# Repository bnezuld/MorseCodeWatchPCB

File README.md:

# MorseCodeWatchPCB

KiCad PCB built for my [Morse Code Smart Watch project](https://github.com/bnezuld/ble_app_morsecode_watch)

with a [Bill of Material](https://github.com/bnezuld/MorseCodeWatchPCB/blob/master/MorseCodeWatch_bom.csv) of:
| Bill of material           |                         |                                                                                |               |
|--------------------------|----------------------------------|------------------------------------------------------------------------------|-----------------|
|PCB:                      |Morse Code Watch layout           |                                                                              |                 |
|Version:                  |1.1                               |                                                                              |                 |
|Designator                |Value                             |Description                                                                   |Footprint Doc    |
|C1, C2, C11, C12, C13, C14|12pF                              |Capacitor, NP0, ±2%                                                           |0402             |
|C3                        |0.8pF                             |Capacitor, NP0, ±5%                                                           |0402             |
|C4, C5, C8                |100nF                             |Capacitor, X7R, ±10%                                                          |0402             |
|C6                        |N.C.                              |Not mounted                                                                   |0402             |
|C7                        |100pF                             |Capacitor, NP0, ±5%                                                           |0402             |
|C9                        |4.7µF                             |Capacitor, X5R, ±10%                                                          |0603             |
|C10                       |1.0µF                             |Capacitor, X7R, ±10%                                                          |0603             |
|C15                       |22pF                              |                                                                              |0402             |
|C16,C17,C18               |10uF                              |                                                                              |0402             |
|C19                       |1.0µF                             |                                                                              |0402             |
|C20                       |2.2uF                             |                                                                              |0402             |
|L1                        |3.9nH                             |High frequency chip inductor ±5%                                              |0402             |
|U1                        |nRF52832-QFAA                     |Multi-protocol Bluetooth Low Energy, ANT and 2.4GHz proprietary system-on-chip|QFN-48           |
|X1                        |32MHz                             |XTAL SMD 2016, 32MHz, Cl=8pF, Total Tol: ±40ppm                               |XTAL_2016        |
|X2                        |32.768kHz                         |XTAL SMD 3215, 32.768kHz, Cl=9pF, Total Tol: ±50ppm                           |XTAL_3215        |
|R1                        |1K                                |                                                                              |0402             |
|R2,R3                     |10K                               |                                                                              |0402             |
|R4,R5                     |47ohm                             |                                                                              |0402             |
|R6                        |28K                               |                                                                              |0402             |
|U2                        |AT42QT1010                        |                                                                              |SOT-23-6         |
|U3                        |CAT24C256                         |                                                                              |Soic-8           |
|U4                        |MCP73831                          |                                                                              |SOT-23-5         |
|U5                        |DRV8836                           |                                                                              |WSON-12-1EP 3x2mm|
|U6                        |TPS78330                          |                                                                              |SOT-23-5         |
|D1                        |Red LED                           |                                                                              |0603             |
|D2                        |Green LED                         |                                                                              |0603             |
|SW1                       |DIP switch 5.08mm x 1.27mm        |                                                                              |                 |
|J1                        |2X5 1.27 mm pitch                 |                                                                              |                 |
|J2                        |USB B micro                       |                                                                              |                 |
|J3, J6                    |JST ACH 1x2                       |touchpad                                                                      |                 |
|J5                        |BatteryHolder Keystone 3034 1x20mm|battery                                                                       |                 |

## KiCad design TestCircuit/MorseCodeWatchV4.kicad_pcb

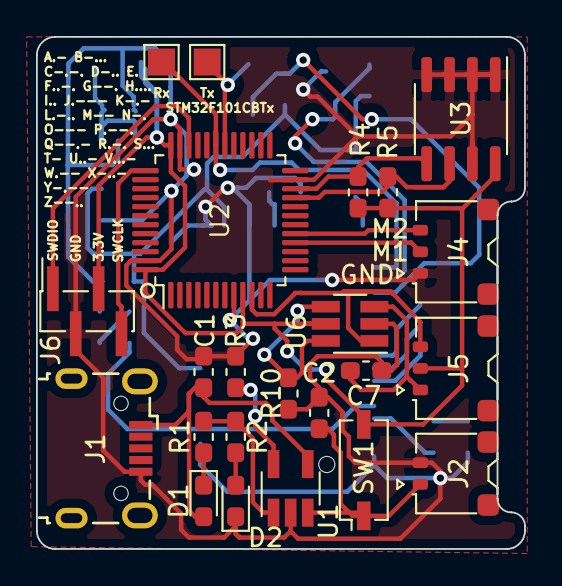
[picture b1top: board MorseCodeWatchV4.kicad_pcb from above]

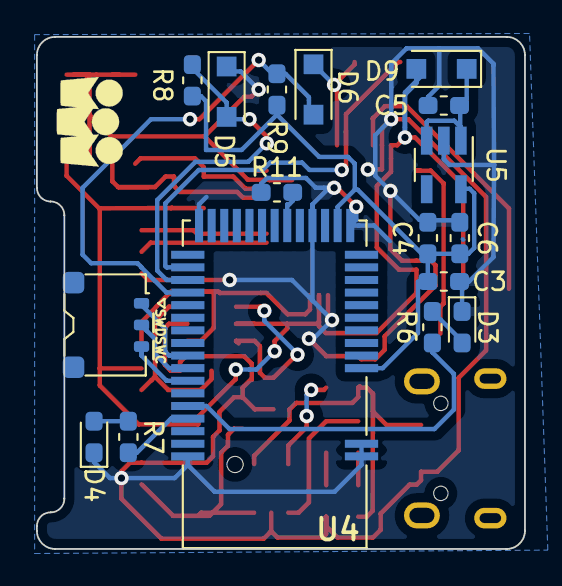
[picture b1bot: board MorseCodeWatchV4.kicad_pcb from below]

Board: 2 copper layers, 27.1 x 28.4 mm, 39 parts (16 on the bottom side), 28 nets.

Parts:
C1, C2: C 10uf; C_0603_1608Metric_Pad1.05x0.95mm_HandSolder
C3, C4: 1uF; C_0603_1608Metric_Pad1.05x0.95mm_HandSolder
C5, C6: 10uF; C_0603_1608Metric_Pad1.05x0.95mm_HandSolder
C7: 22pF; C_0603_1608Metric_Pad1.05x0.95mm_HandSolder
D1: LED RED; LED_0603_1608Metric_Pad1.05x0.95mm_HandSolder
D2: LED GREEN; LED_0603_1608Metric_Pad1.05x0.95mm_HandSolder
D3: LED RED; D_0603_1608Metric_Pad1.05x0.95mm_HandSolder
D4: LED BLUE; D_0603_1608Metric_Pad1.05x0.95mm_HandSolder
D5, D6: 1N4148; D_SOD-123F
D9: MBR120; D_SOD-123F
J1: USB_B_Micro; USB_Micro-B_Wuerth_629105150521
J2: Conn_01x02_Male LiPo Battery; JST_ACH_BM02B-ACHSS-GAN-ETF_1x02-1MP_P1.20mm_Vertical
J4, J5: Conn_01x03; JST_ACH_BM03B-ACHSS-GAN-ETF_1x03-1MP_P1.20mm_Vertical
J6: Conn_01x04_Female; PinHeader_1x04_P1.27mm_Vertical_SMD_Pin1Right
R1, R2, R4, R5: R; R_0603_1608Metric_Pad1.05x0.95mm_HandSolder
R3: R 10K; R_0603_1608Metric_Pad1.05x0.95mm_HandSolder
R6, R7, R10: 1K; R_0603_1608Metric_Pad1.05x0.95mm_HandSolder
R8, R9: 100K; R_0603_1608Metric_Pad1.05x0.95mm_HandSolder
R11: 2K; R_0603_1608Metric_Pad1.05x0.95mm_HandSolder
Rx: TestPoint_Pad_1.5x1.5mm
SW1: SW_DIP_x01; SW_DIP_SPSTx01_Slide_Copal_CHS-01A_W5.08mm_P1.27mm_JPin
Tx: TestPoint_Pad_1.5x1.5mm
U1: MCP73831-2-OT; SOT-23-5_HandSoldering
U2: STM32F101CBTx; LQFP-48_7x7mm_P0.5mm
U3: CAT24C256; SOIC-8_3.9x4.9mm_P1.27mm
U4: NRF51822_MODULE_MDBT40; BLE_MODULE_RAYTAC_MDBT40
U5: MIC5225-3.3; SOT-23-5_HandSoldering
U6: AT42QT1010-TSHR; SOT-23-6_Handsoldering

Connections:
3.3V: C3.1, C4.1, C6.1, R8.2, R9.2, U4.3, U4.14, U5.5
/CONNECTED_LED: R7.1, U4.39
/CTS_3V: D5.2, R8.1, U4.28
/MODE_3V: R11.1, U4.18
/MODE_LED: R6.1, U4.38
/MainSwitch: J5.3, U2.10, U6.1
/Motor1: J4.2, U2.16
/Motor2: J4.3, U2.17
/PROG: R3.1, U1.5
/Rx: Rx.1, U2.31, U4.27
/SCL: R4.2, U2.21, U3.6
/SDA: R5.2, U2.22, U3.5
/STAT: R1.2, R2.2, U1.1
/SWCLK: J6.4, U2.37
/SWDIO: J6.1, U2.34
/TOG-AHLB: R10.1, U6.4, U6.6
/TXD_3V: D6.2, R9.1, U4.29
/TouchPad: C7.1, J5.1, U6.3
/Tx: D6.1, Tx.1, U2.30
/VBAT: D9.2, J5.2, J6.3, R4.1, R5.1, SW1.2, U2.9, U2.24, U2.36, U2.48, U3.8, U6.5
/VBAT-IN: C2.1, J2.1, SW1.1, U1.3
/VCC: C1.1, D1.2, J1.1, U1.4
GND: C1.2, C2.2, C3.2, C4.2, C5.2, C6.2, C7.2, D2.1, D3.1, D4.1, D5.1, J1.5, J2.2, J4.1, J6.2, R3.2, R10.2, R11.2, U1.2, U2.8, U2.23, U2.35, U2.47, U3.1, U3.2, U3.3, U3.4, U3.7, U4.1, U4.2, U4.13, U4.16, U4.25, U4.42, U5.2, U6.2
unnamed: C5.1, D9.1, U5.1, U5.3
unnamed: D1.1, R1.1
unnamed: D2.2, R2.1
unnamed: D3.2, R6.2
unnamed: D4.2, R7.2

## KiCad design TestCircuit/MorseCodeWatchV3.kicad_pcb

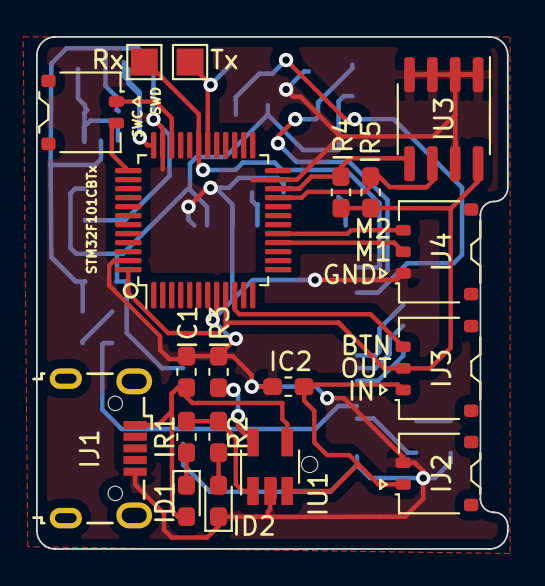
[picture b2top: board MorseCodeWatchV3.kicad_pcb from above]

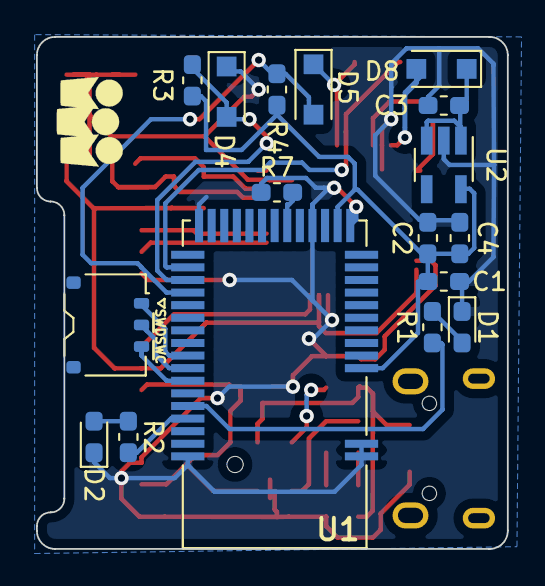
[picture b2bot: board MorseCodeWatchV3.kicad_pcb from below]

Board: 2 copper layers, 26.2 x 28.4 mm, 34 parts (16 on the bottom side), 24 nets.

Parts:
C1, C2: 1uF; C_0603_1608Metric_Pad1.05x0.95mm_HandSolder
C3, C4: 10uF; C_0603_1608Metric_Pad1.05x0.95mm_HandSolder
D1: RED; D_0603_1608Metric_Pad1.05x0.95mm_HandSolder
D2: GREEN; D_0603_1608Metric_Pad1.05x0.95mm_HandSolder
D4, D5, D8: MBR120; D_SOD-123F
IC1, IC2: C 10uf; C_0603_1608Metric_Pad1.05x0.95mm_HandSolder
ID1: LED RED; LED_0603_1608Metric_Pad1.05x0.95mm_HandSolder
ID2: LED GREEN; LED_0603_1608Metric_Pad1.05x0.95mm_HandSolder
IJ1: USB_B_Micro; USB_Micro-B_Wuerth_629105150521
IJ2: Conn_01x02_Male LiPo Battery; JST_ACH_BM02B-ACHSS-GAN-ETF_1x02-1MP_P1.20mm_Vertical
IJ3, IJ4: JST_ACH_BM03B-ACHSS-GAN-ETF_1x03-1MP_P1.20mm_Vert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; JST_ACH_BM03B-ACHSS-GAN-ETF_1x03-1MP_P1.20mm_Vertical
IR1, IR2, IR4, IR5: R; R_0603_1608Metric_Pad1.05x0.95mm_HandSolder
IR3: R 10K; R_0603_1608Metric_Pad1.05x0.95mm_HandSolder
IU1: MCP73831-2-OT; SOT-23-5_HandSoldering
IU3: CAT24C256; SOIC-8_3.9x4.9mm_P1.27mm
R1, R2: 1K; R_0603_1608Metric_Pad1.05x0.95mm_HandSolder
R3, R4, R7: 100K; R_0603_1608Metric_Pad1.05x0.95mm_HandSolder
Rx: TestPoint_Pad_1.5x1.5mm
STM32F101CBTx: STM32F101CBTx; LQFP-48_7x7mm_P0.5mm
Tx: TestPoint_Pad_1.5x1.5mm
U1: NRF51822_MODULE_MDBT40; BLE_MODULE_RAYTAC_MDBT40
U2: MIC5225-3.3; SOT-23-5_HandSoldering

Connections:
3.3V: C1.1, C2.1, C4.1, R3.2, R4.2, U1.3, U1.14, U2.5
/CONNECTED_LED: R2.1, U1.39
/CTS_3V: D4.2, R3.1, U1.28
/MODE_3V: R7.1, U1.18
/MODE_LED: R1.1, U1.38
/MainSwitch: IJ3.3, STM32F101CBTx.10
/Motor1: IJ4.2, STM32F101CBTx.16
/Motor2: IJ4.3, STM32F101CBTx.17
/PROG: IR3.1, IU1.5
/Rx: Rx.1, STM32F101CBTx.31, U1.27
/SCL: IR4.2, IU3.6, STM32F101CBTx.21
/SDA: IR5.2, IU3.5, STM32F101CBTx.22
/STAT: IR1.2, IR2.2, IU1.1
/TXD_3V: D5.2, R4.1, U1.29
/Tx: D5.1, STM32F101CBTx.30, Tx.1
/VBAT: D8.2, IC2.1, IJ2.1, IJ3.1, IJ3.2, IR4.1, IR5.1, IU1.3, IU3.8, STM32F101CBTx.9, STM32F101CBTx.24, STM32F101CBTx.36, STM32F101CBTx.48
/VCC: IC1.1, ID1.2, IJ1.1, IU1.4
GND: C1.2, C2.2, C3.2, C4.2, D1.1, D2.1, D4.1, IC1.2, IC2.2, ID2.1, IJ1.5, IJ2.2, IJ4.1, IR3.2, IU1.2, IU3.1, IU3.2, IU3.3, IU3.4, IU3.7, R7.2, STM32F101CBTx.8, STM32F101CBTx.23, STM32F101CBTx.35, STM32F101CBTx.47, U1.1, U1.2, U1.13, U1.16, U1.25, U1.42, U2.2
unnamed: C3.1, D8.1, U2.1, U2.3
unnamed: D1.2, R1.2
unnamed: D2.2, R2.2
unnamed: ID1.1, IR1.1
unnamed: ID2.2, IR2.1
unnamed: STM32F101CBTx.4, U2.4

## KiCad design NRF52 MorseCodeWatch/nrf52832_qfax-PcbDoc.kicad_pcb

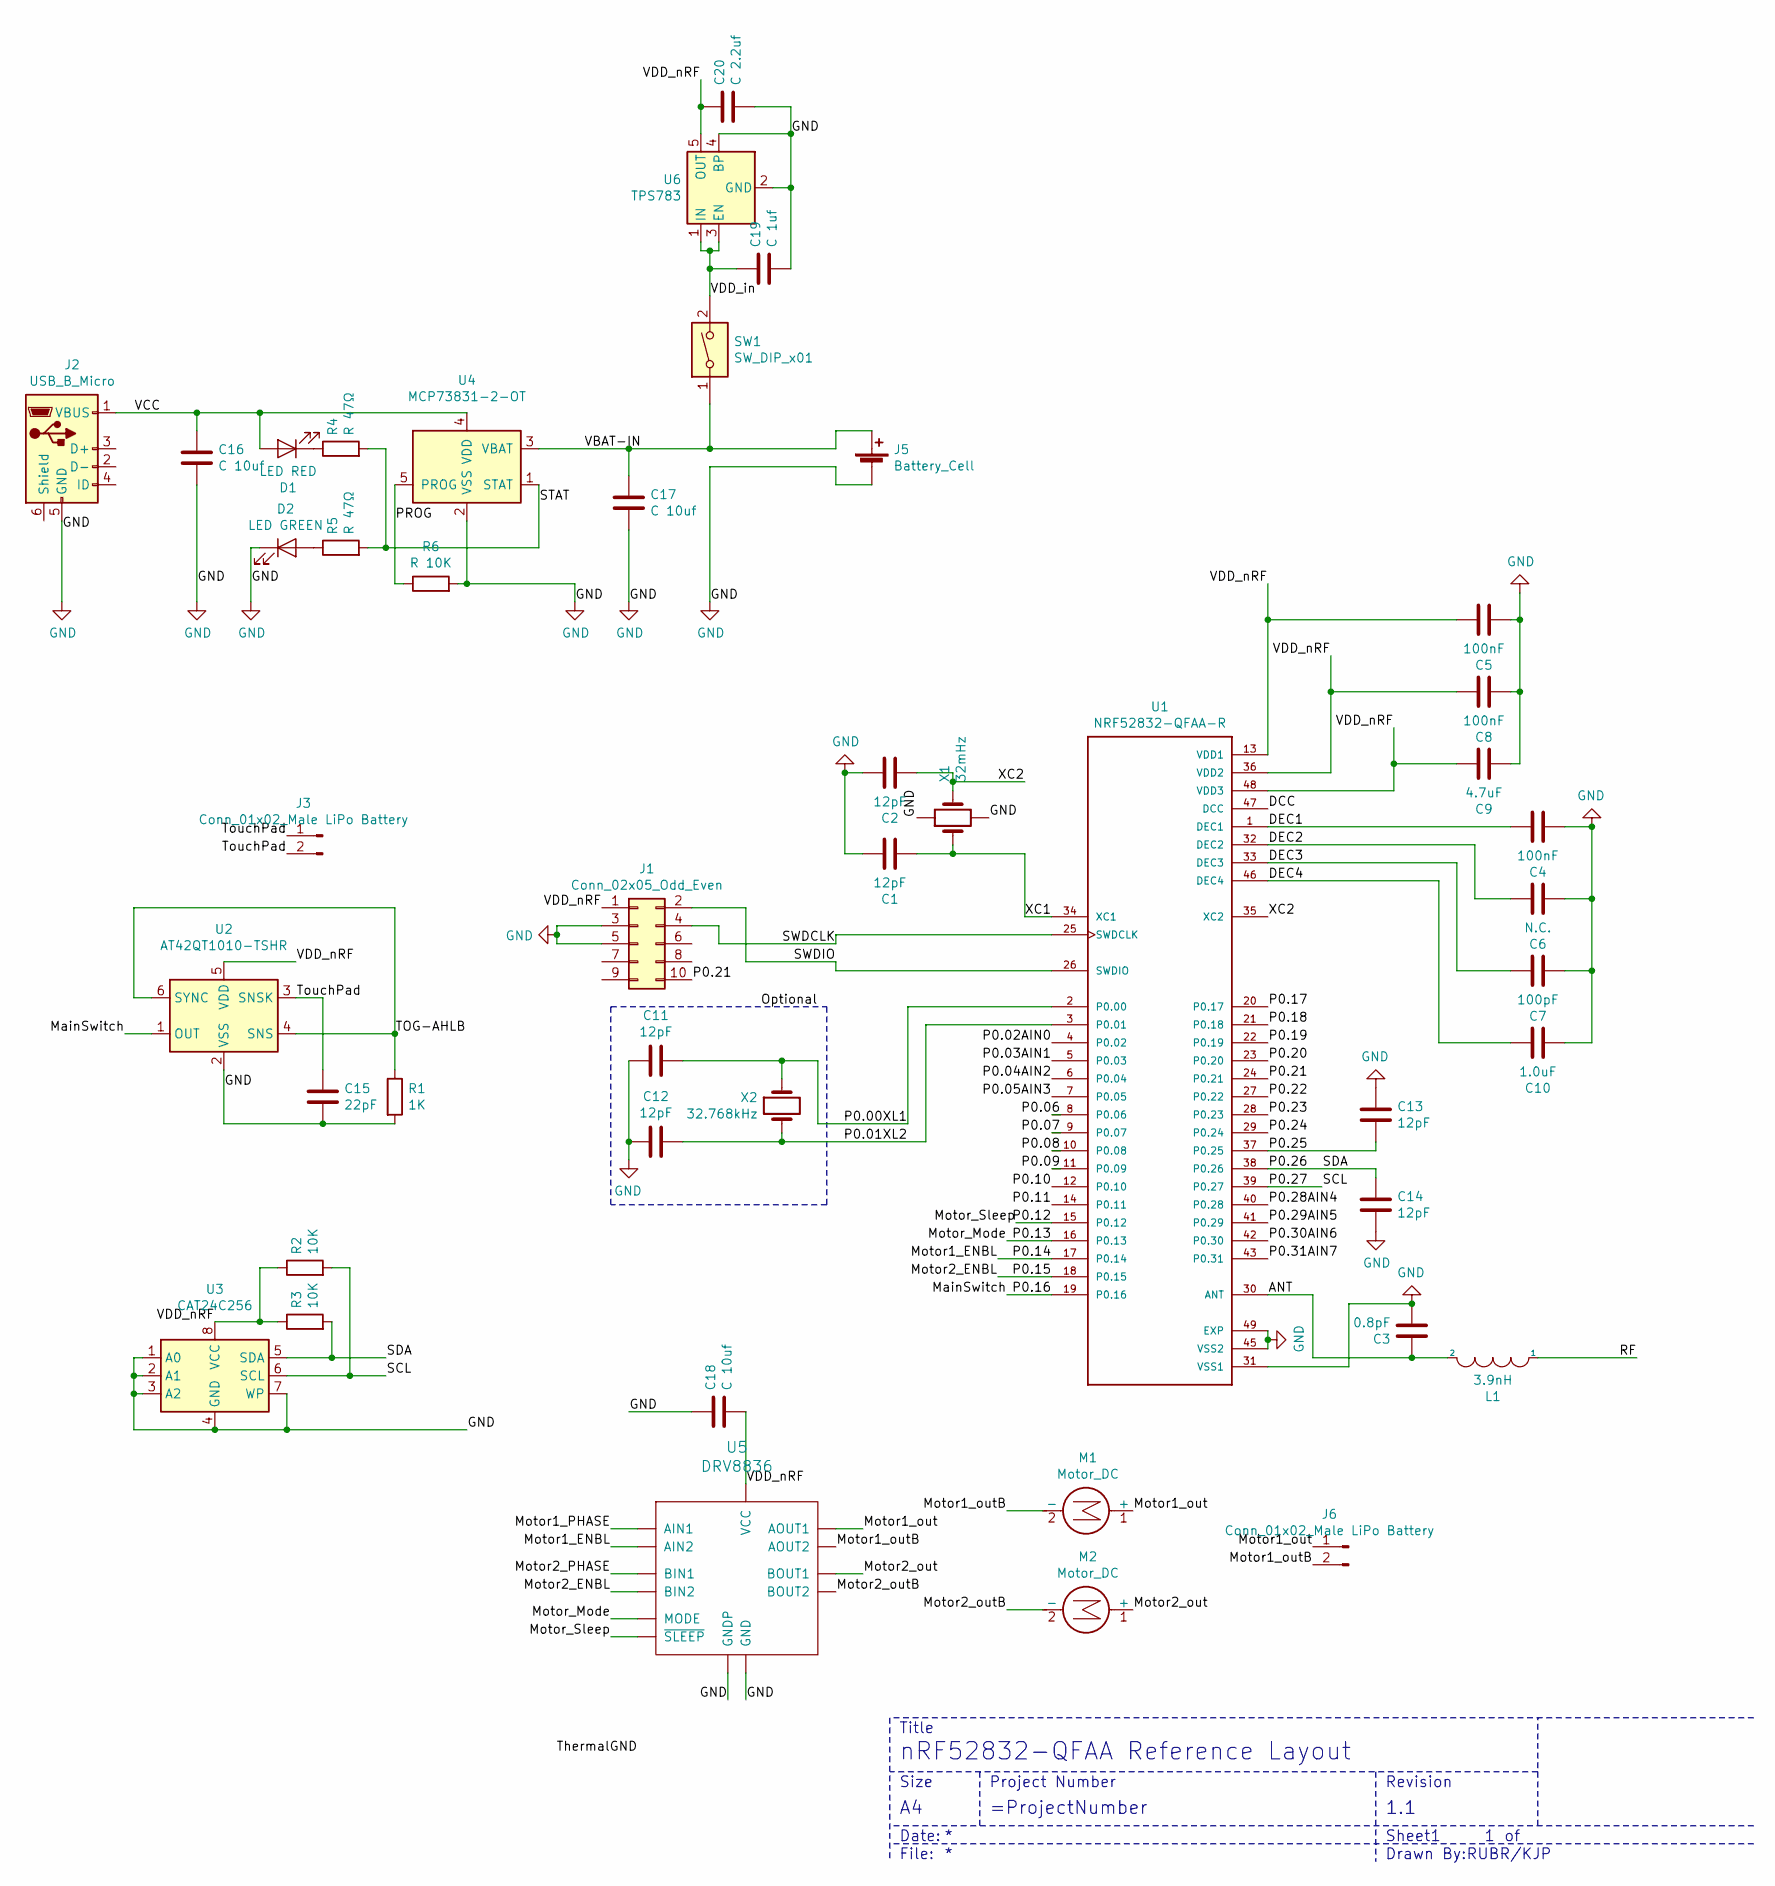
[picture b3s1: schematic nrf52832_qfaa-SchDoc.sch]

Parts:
C1, C2, C11, C12, C13, C14: 12pF; C_0603_1608Metric_Pad1.05x0.95mm_HandSolder
C3: 0.8pF; C_0603_1608Metric_Pad1.05x0.95mm_HandSolder
C4, C5, C8: 100nF; C_0603_1608Metric_Pad1.05x0.95mm_HandSolder
C6: N.C.; C_0603_1608Metric_Pad1.05x0.95mm_HandSolder
C7: 100pF; C_0603_1608Metric_Pad1.05x0.95mm_HandSolder
C9: 4.7uF; C_0603_1608Metric_Pad1.05x0.95mm_HandSolder
C10: 1.0uF; C_0603_1608Metric_Pad1.05x0.95mm_HandSolder
C15: 22pF; C_0402_1005Metric
C16, C17, C18: C 10uf; C_0402_1005Metric
C19: C 1uf; C_0402_1005Metric
C20: C 2.2uf; C_0402_1005Metric
D1: LED RED; LED_0603_1608Metric
D2: LED GREEN; LED_0603_1608Metric
J1: Conn_02x05_Odd_Even
J2: USB_B_Micro; USB_Micro-B_Wuerth_629105150521
J3, J6: Conn_01x02_Male LiPo Battery; JST_ACH_BM02B-ACHSS-GAN-ETF_1x02-1MP_P1.20mm_Vertical
J5: Battery_Cell; BatteryHolder_Keystone_3034_1x20mm
L1: 3.9nH; L_0603_1608Metric_Pad1.05x0.95mm_HandSolder
M1, M2: Motor_DC; JST_ACH_BM02B-ACHSS-GAN-ETF_1x02-1MP_P1.20mm_Vertical
R1: 1K; R_0402_1005Metric
R2, R3: 10K; R_0402_1005Metric
R4, R5: R 47Ω; R_0402_1005Metric
R6: R 10K; R_0402_1005Metric
SW1: SW_DIP_x01; SW_DIP_SPSTx01_Slide_Copal_CHS-01A_W5.08mm_P1.27mm_JPin
U1: NRF52832-QFAA-R; QFN40P600X600X90-49N
U2: AT42QT1010-TSHR; SOT-23-6
U3: CAT24C256; SOIC-8_3.9x4.9mm_P1.27mm
U4: MCP73831-2-OT; SOT-23-5
U5: DRV8836; WSON-12-1EP_3x2mm_P0.5mm_EP1x2.65
U6: TPS783; SOT-23-5
X1: 32mHz
X2: 32.768kHz; Crystal_SMD_3225-4Pin_3.2x2.5mm_HandSoldering

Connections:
/ANT: C3.2, L1.2, U1.30 (ANT)
/DCC: U1.47 (DCC)
/DEC1: C4.2, U1.1 (DEC1)
/DEC2: C6.2, U1.32 (DEC2)
/DEC3: C7.2, U1.33 (DEC3)
/DEC4: C10.1, U1.46 (DEC4)
/MainSwitch: U1.19 (P0.16), U2.1 (OUT)
/Motor1_ENBL: U1.17 (P0.14), U5.9 (AIN2)
/Motor1_PHASE: U5.10 (AIN1)
/Motor1_out: J6.1, M1.1 (+), U5.2 (AOUT1)
/Motor1_outB: J6.2, M1.2 (-), U5.3 (AOUT2)
/Motor2_ENBL: U1.18 (P0.15), U5.7 (BIN2)
/Motor2_PHASE: U5.8 (BIN1)
/Motor2_out: M2.1 (+), U5.4 (BOUT1)
/Motor2_outB: M2.2 (-), U5.5 (BOUT2)
/Motor_Mode: U1.16 (P0.13), U5.11 (MODE)
/Motor_Sleep: U1.15 (P0.12), U5.12 (~SLEEP)
/P0.00XL1: C11.2, U1.2 (P0.00), X2.1
/P0.01XL2: C12.2, U1.3 (P0.01), X2.2
/P0.02AIN0: U1.4 (P0.02)
/P0.03AIN1: U1.5 (P0.03)
/P0.04AIN2: U1.6 (P0.04)
/P0.05AIN3: U1.7 (P0.05)
/P0.06: U1.8 (P0.06)
/P0.07: U1.9 (P0.07)
/P0.08: U1.10 (P0.08)
/P0.09: U1.11 (P0.09)
/P0.10: U1.12 (P0.10)
/P0.11: U1.14 (P0.11)
/P0.17: U1.20 (P0.17)
/P0.18: U1.21 (P0.18)
/P0.19: U1.22 (P0.19)
/P0.20: U1.23 (P0.20)
/P0.21: J1.10, U1.24 (P0.21)
/P0.22: U1.27 (P0.22)
/P0.23: U1.28 (P0.23)
/P0.24: U1.29 (P0.24)
/P0.25: C13.1, U1.37 (P0.25)
/P0.26: C14.1, R3.2, U1.38 (P0.26), U3.5 (SDA)
/P0.27: R2.2, U1.39 (P0.27), U3.6 (SCL)
/P0.28AIN4: U1.40 (P0.28)
/P0.29AIN5: U1.41 (P0.29)
/P0.30AIN6: U1.42 (P0.30)
/P0.31AIN7: U1.43 (P0.31)
/PROG: R6.1, U4.5 (PROG)
/RF: L1.1
/STAT: R4.2, R5.2, U4.1 (STAT)
/SWDCLK: J1.4, U1.25 (SWDCLK)
/SWDIO: J1.2, U1.26 (SWDIO)
/TOG-AHLB: R1.1, U2.4 (SNS), U2.6 (SYNC)
/TouchPad: C15.1, J3.1, J3.2, U2.3 (SNSK)
/VBAT-IN: C17.1, J5.1 (+), SW1.1, U4.3 (VBAT); also elsewhere on the board
/VCC: C16.1, D1.2 (A), J2.1 (VBUS), U4.4 (VDD)
/VDD_in: C19.1, SW1.2, U6.1 (IN), U6.3 (EN); also elsewhere on the board
/VDD_nRF: C5.2, C8.2, C9.2, C18.2, C20.1, J1.1, R2.1, R3.1, U1.13 (VDD1), U1.36 (VDD2), U1.48 (VDD3), U2.5 (VDD), U3.8 (VCC), U5.1 (VCC), U6.5 (OUT); also elsewhere on the board
/XC1: C1.1, U1.34 (XC1), X1.1
/XC2: C2.1, U1.35 (XC2), X1.2
GND: C1.2, C2.2, C3.1, C4.1, C5.1, C6.1, C7.1, C8.1, C9.1, C10.2, C11.1, C12.1, C13.2, C14.2, C15.2, C16.2, C17.2, C18.1, C19.2, C20.2, D2.1 (K), J1.3, J1.5, J2.5 (GND), J5.2 (-), R1.2, R6.2, U1.31 (VSS1), U1.45 (VSS2), U1.49 (EXP), U2.2 (VSS), U3.1 (A0), U3.2 (A1), U3.3 (A2), U3.4 (GND), U3.7 (WP), U4.2 (VSS), U5.6 (GND), U5.PAD (GNDP), U6.2 (GND), U6.4 (BP), X1.3 (GND), X1.4 (GND); also elsewhere on the board
unnamed: D1.1 (K), R4.1
unnamed: D2.2 (A), R5.1

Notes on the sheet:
Title
Size
Project Number
Date:
File:
Sheet of
Drawn By:
Revision
nRF52832-QFAA Reference Layout
1.1
RUBR/KJP
=ProjectNumber

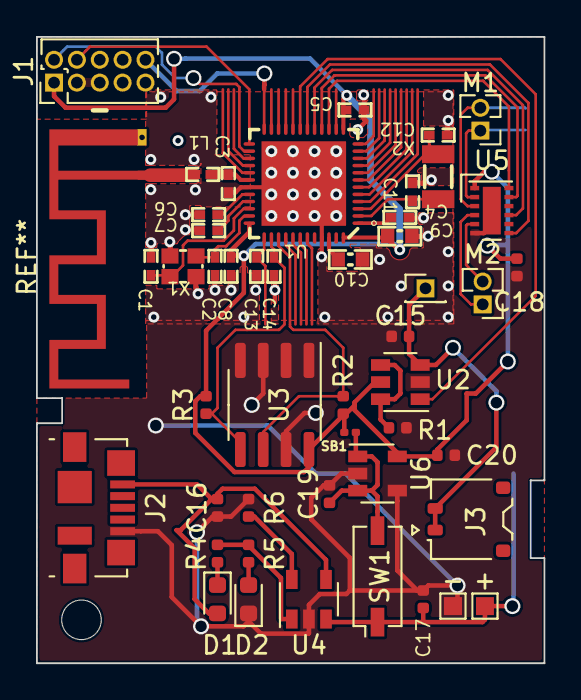
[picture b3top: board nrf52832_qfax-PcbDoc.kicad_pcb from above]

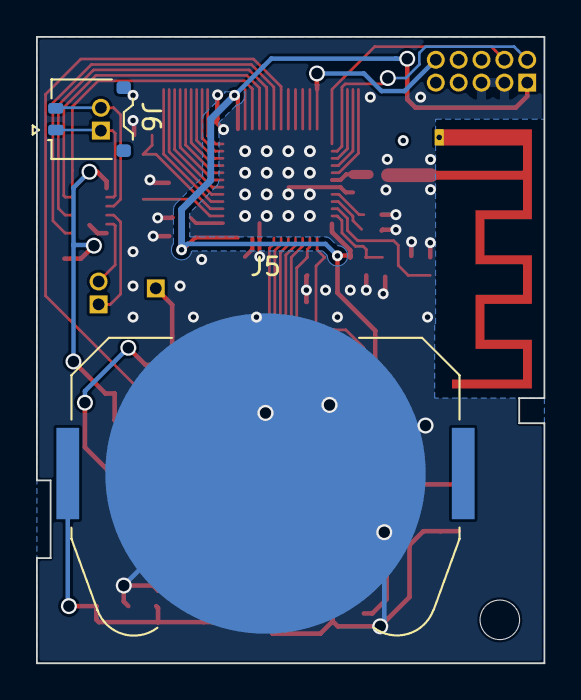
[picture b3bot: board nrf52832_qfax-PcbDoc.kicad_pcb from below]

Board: 2 copper layers, 28.2 x 34.8 mm, 48 parts (2 on the bottom side), 35 nets.

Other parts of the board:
+: TestPoint_Pad_1.0x1.0mm
-: TestPoint_Pad_1.0x1.0mm
SB1: R_0201_0603Metric

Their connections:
/VBAT-IN: +.1; also elsewhere on the board
/VDD_in: SB1.2; also elsewhere on the board
/VDD_nRF: SB1.1; also elsewhere on the board
GND: -.1; also elsewhere on the board

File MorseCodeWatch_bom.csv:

Bill of material,,,
PCB:,Morse Code Watch layout,,
Version:,1.1,,
Designator,Value,Description,Footprint Doc
"C1, C2, C11, C12, C13, C14",12pF,"Capacitor, NP0, ±2%",0402
C3,0.8pF,"Capacitor, NP0, ±5%",0402
"C4, C5, C8",100nF,"Capacitor, X7R, ±10%",0402
C6,N.C.,Not mounted,0402
C7,100pF,"Capacitor, NP0, ±5%",0402
C9,4.7µF,"Capacitor, X5R, ±10%",0603
C10,1.0µF,"Capacitor, X7R, ±10%",0603
C15,22pF,,
"C16,C17,C18",10uF,,
L1,3.9nH,High frequency chip inductor ±5%,0402
U1,nRF52832-QFAA,"Multi-protocol Bluetooth Low Energy, ANT and 2.4GHz proprietary system-on-chip",QFN-48
X1,32MHz,"XTAL SMD 2016, 32MHz, Cl=8pF, Total Tol: ±40ppm",XTAL_2016
X2,32.768kHz,"XTAL SMD 3215, 32.768kHz, Cl=9pF, Total Tol: ±50ppm",XTAL_3215
R1,1K,,
"R2,R3",10K,,
"R4,R5",47ohm,,
R6,28K,,
U2,AT42QT1010,,
U3,CAT24C256,,
U4,MCP73831,,
U5,DRV8836,,
D1,Red LED,,
D2,Green LED,,
SW1,DIP switch,,
J1,2X5 1.27 mm pitch,,
J2,USB B micro,,
J3,battery,,

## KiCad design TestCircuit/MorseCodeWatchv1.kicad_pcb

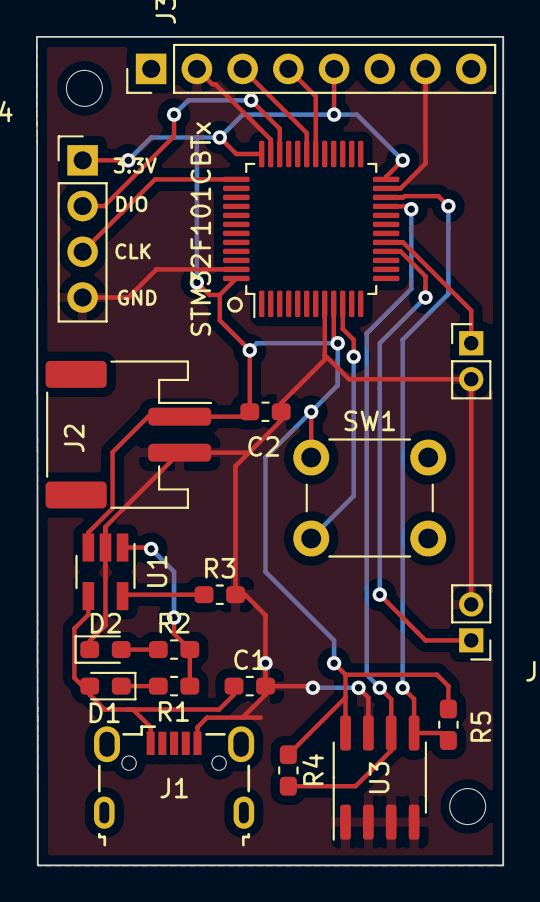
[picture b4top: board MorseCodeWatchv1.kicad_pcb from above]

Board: 2 copper layers, 25.9 x 46.0 mm, 19 parts (0 on the bottom side), 16 nets.

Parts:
C1, C2: C 10uf; C_0603_1608Metric_Pad1.05x0.95mm_HandSolder
D1: LED RED; LED_0603_1608Metric_Pad1.05x0.95mm_HandSolder
D2: LED GREEN; LED_0603_1608Metric_Pad1.05x0.95mm_HandSolder
J1: USB_B_Micro; USB_Micro-B_Wuerth_629105150521
J2: Conn_01x02_Male LiPo Battery; JST_PH_S2B-PH-SM4-TB_1x02-1MP_P2.00mm_Horizontal
J3: Conn_01x08_Female; PinHeader_1x08_P2.54mm_Vertical
J4: Conn_01x04_Female; PinHeader_1x04_P2.54mm_Vertical
J5, J6: Conn_01x02_Female; PinHeader_1x02_P2.00mm_Vertical
R1, R2, R4, R5: R; R_0603_1608Metric_Pad1.05x0.95mm_HandSolder
R3: R 10K; R_0603_1608Metric_Pad1.05x0.95mm_HandSolder
STM32F101CBTx: STM32F101CBTx; LQFP-48_7x7mm_P0.5mm
SW1: SW_Push; SW_PUSH_6mm_H13mm
U1: MCP73831-2-OT; SOT-23-5_HandSoldering
U3: CAT24C256; SOIC-8_3.9x4.9mm_P1.27mm

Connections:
/MainSwitch: STM32F101CBTx.10, SW1.2
/Motor1: J5.1, STM32F101CBTx.16
/Motor2: J6.1, STM32F101CBTx.17
/PROG: R3.1, U1.5
/Rx: J3.3, STM32F101CBTx.31
/SCL: R4.2, STM32F101CBTx.21, U3.6
/SDA: R5.2, STM32F101CBTx.22, U3.5
/STAT: R1.2, R2.2, U1.1
/SWCLK: J4.3, STM32F101CBTx.37
/SWDIO: J4.2, STM32F101CBTx.34
/Tx: J3.4, STM32F101CBTx.30
/VBAT: C2.1, J2.1, J3.5, J4.1, R4.1, R5.1, STM32F101CBTx.9, STM32F101CBTx.24, STM32F101CBTx.36, STM32F101CBTx.48, SW1.1, U1.3, U3.8
/VCC: C1.1, D1.2, J1.1, U1.4
GND: C1.2, C2.2, D2.1, J1.5, J2.2, J3.2, J3.7, J4.4, J5.2, J6.2, R3.2, STM32F101CBTx.8, STM32F101CBTx.23, STM32F101CBTx.35, STM32F101CBTx.47, U1.2, U3.1, U3.2, U3.3, U3.4, U3.7
unnamed: D1.1, R1.1
unnamed: D2.2, R2.1

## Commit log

2020-06-06 adding correct ground
2020-07-02 minor fixes
    minor layout changes to pcb
2020-07-27 adding routing for a jst connection
    adding routing for a jst connection to the touchpad, and a test prob area for the battery
2020-07-27 cleaning up and adding BOM
    added bill of material and cleaned up unused stuff
2020-07-27 adding BOM
    change .gitignore to allow csv files
2020-07-27 Update README.md
    add correct link to Morse Code Watch project
2020-07-27 update PCB with voltage regulator
    using a voltage regulator now with the PCB design.
    update BOM
